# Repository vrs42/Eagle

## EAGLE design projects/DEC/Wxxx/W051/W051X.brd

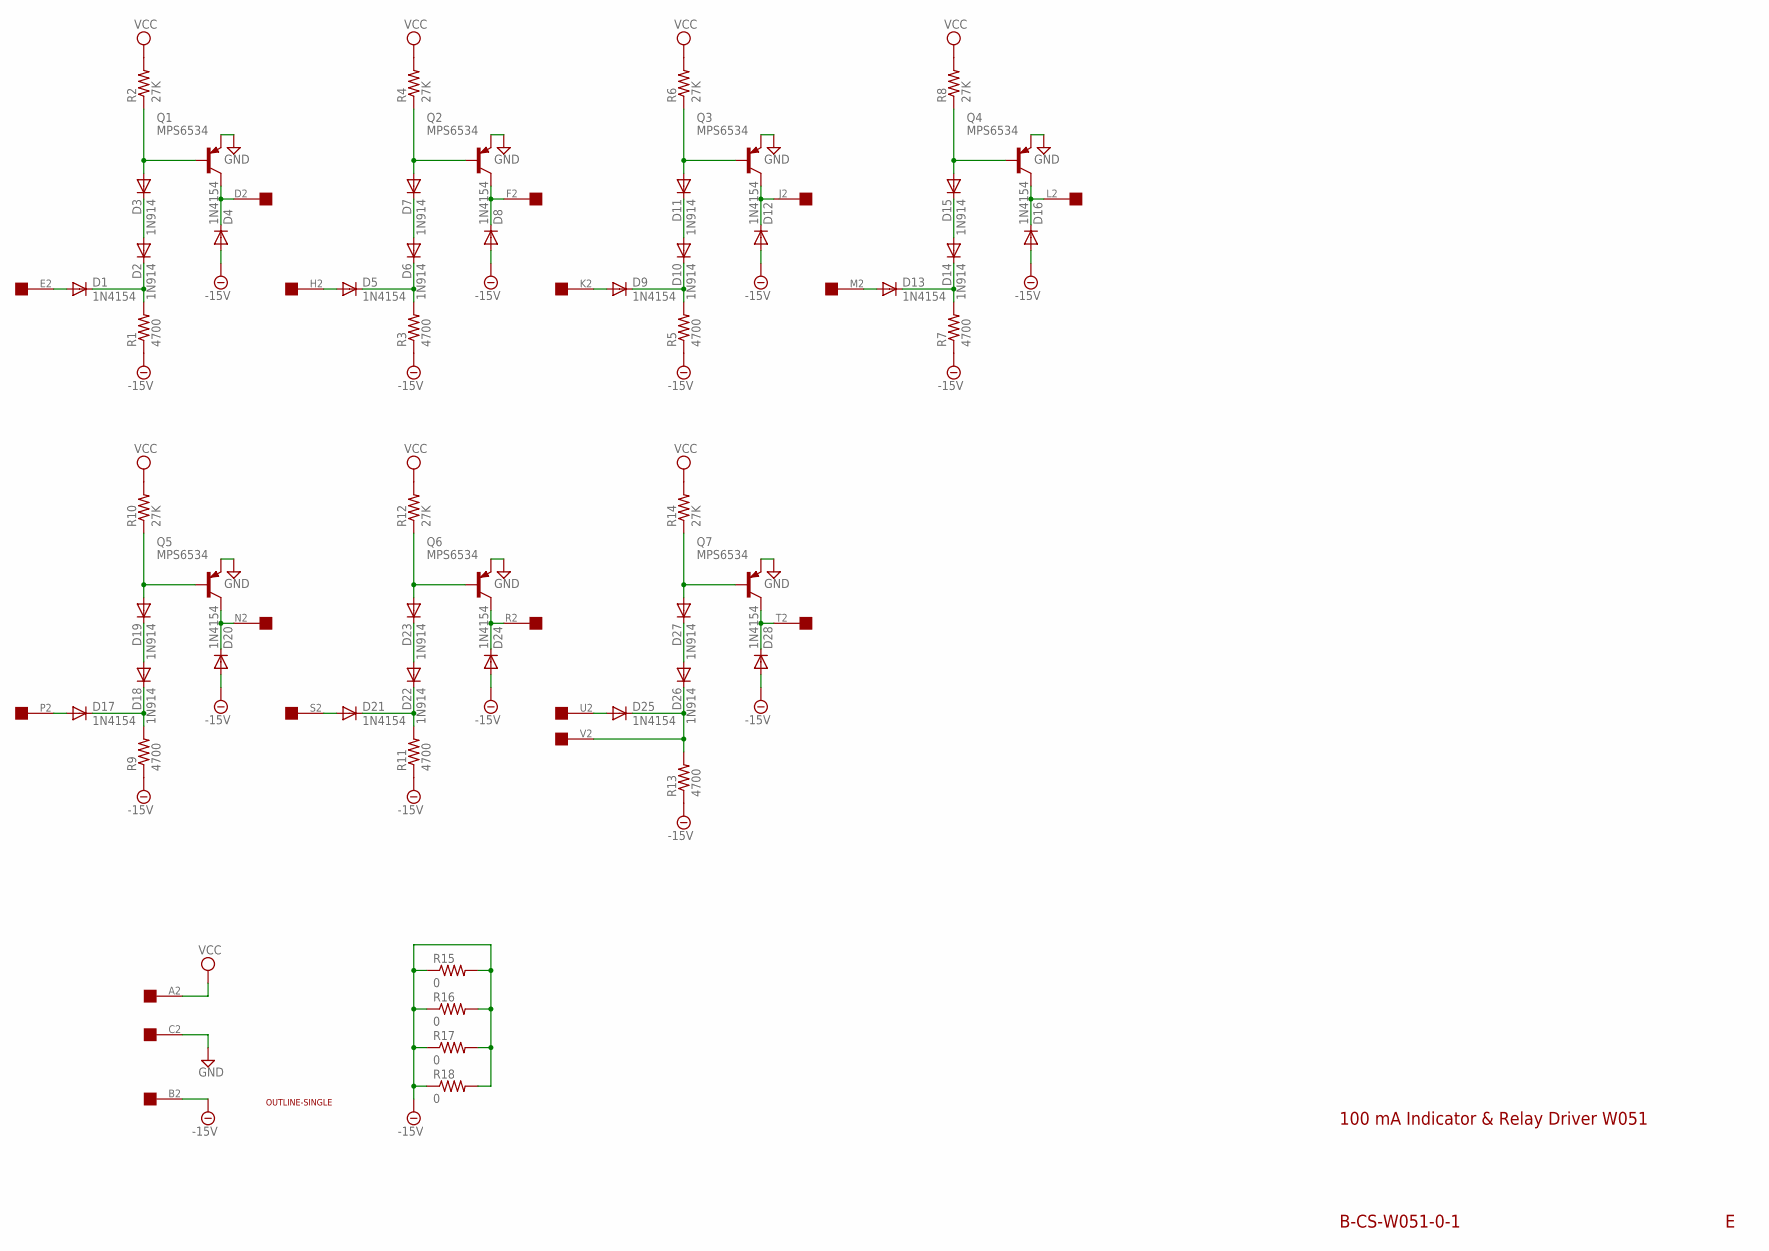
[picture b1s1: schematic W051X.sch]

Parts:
D1, D4, D5, D8, D9, D12, D13, D16, D17, D20, D21, D24, D25, D28: 1N4154; DO35-10
D2, D3, D6, D7, D10, D11, D14, D15, D18, D19, D22, D23, D26, D27: 1N914; DO35-10
Q1, Q2, Q3, Q4, Q5, Q6, Q7: MPS6534; TO5
R1, R3, R5, R7, R9, R11, R13: 4700; 0207/10
R2, R4, R6, R8, R10, R12, R14: 27K; 0207/10
R15, R16, R17, R18: 0; 0207/10
U$1: OUTLINE-SINGLE; SINGLE
U$2: EDGE-1; EDGE-CON1

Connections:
-15V: D4.A, D8.A, D12.A, D16.A, D20.A, D24.A, D28.A, R1.1, R3.1, R5.1, R7.1, R9.1, R11.1, R13.1, R15.1, R15.2, R16.1, R16.2, R17.1, R17.2, R18.1, R18.2, U$2.B2
GND: Q1.1 (E), Q2.1 (E), Q3.1 (E), Q4.1 (E), Q5.1 (E), Q6.1 (E), Q7.1 (E), U$2.C2
unnamed: D1.C, D2.C, R1.2
unnamed: D2.A, D3.C
unnamed: D3.A, Q1.2 (B), R2.1
unnamed: D4.C, Q1.3 (C), U$2.D2
unnamed: D1.A, U$2.E2
unnamed: D5.C, D6.C, R3.2
unnamed: D6.A, D7.C
unnamed: D7.A, Q2.2 (B), R4.1
unnamed: D8.C, Q2.3 (C), U$2.F2
unnamed: D5.A, U$2.H2
unnamed: D9.C, D10.C, R5.2
unnamed: D10.A, D11.C
unnamed: D11.A, Q3.2 (B), R6.1
unnamed: D12.C, Q3.3 (C), U$2.J2
unnamed: D9.A, U$2.K2
unnamed: D13.C, D14.C, R7.2
unnamed: D14.A, D15.C
unnamed: D15.A, Q4.2 (B), R8.1
unnamed: D16.C, Q4.3 (C), U$2.L2
unnamed: D13.A, U$2.M2
unnamed: D17.C, D18.C, R9.2
unnamed: D18.A, D19.C
unnamed: D19.A, Q5.2 (B), R10.1
unnamed: D28.C, Q7.3 (C), U$2.T2
unnamed: D17.A, U$2.P2
unnamed: D21.C, D22.C, R11.2
unnamed: D22.A, D23.C
unnamed: D23.A, Q6.2 (B), R12.1
unnamed: D24.C, Q6.3 (C), U$2.R2
unnamed: D21.A, U$2.S2
unnamed: D25.C, D26.C, R13.2, U$2.V2
unnamed: D26.A, D27.C
unnamed: D27.A, Q7.2 (B), R14.1
unnamed: D20.C, Q5.3 (C), U$2.N2
unnamed: D25.A, U$2.U2
VCC: R2.2, R4.2, R6.2, R8.2, R10.2, R12.2, R14.2, U$2.A2

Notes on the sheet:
B-CS-W051-0-1
100 mA Indicator & Relay Driver W051

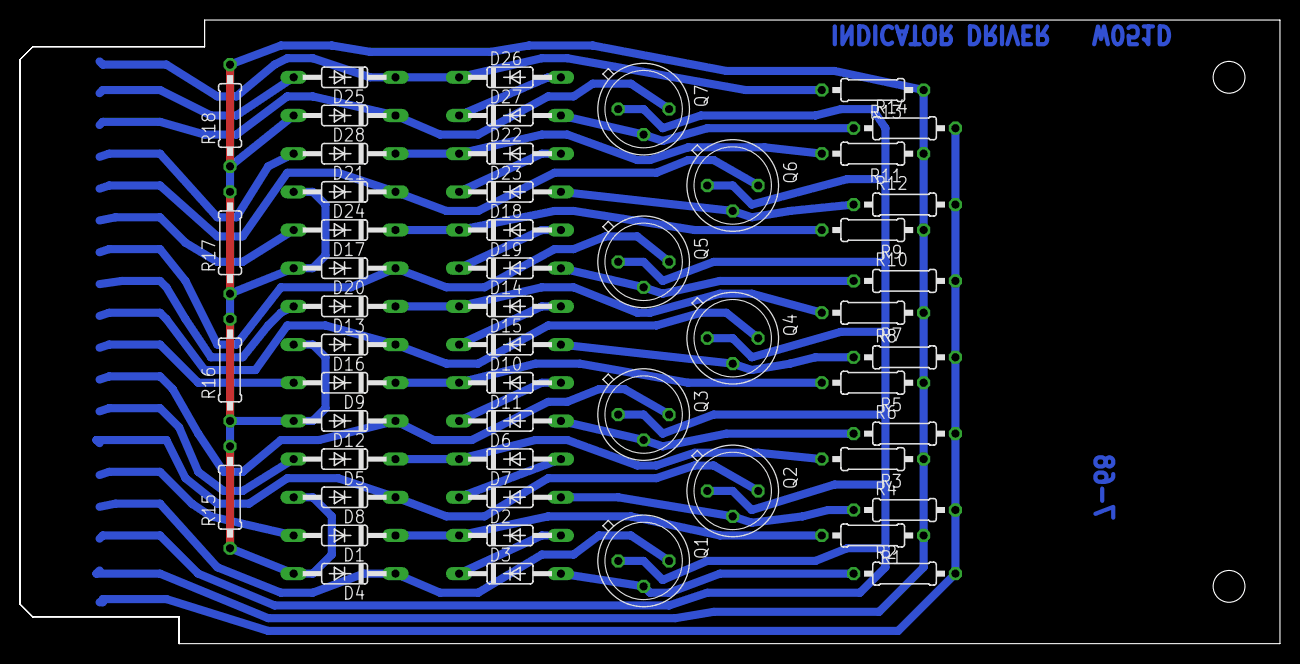
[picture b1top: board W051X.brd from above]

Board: 2 copper layers, 125.7 x 62.2 mm, 55 parts (0 on the bottom side), 38 nets.

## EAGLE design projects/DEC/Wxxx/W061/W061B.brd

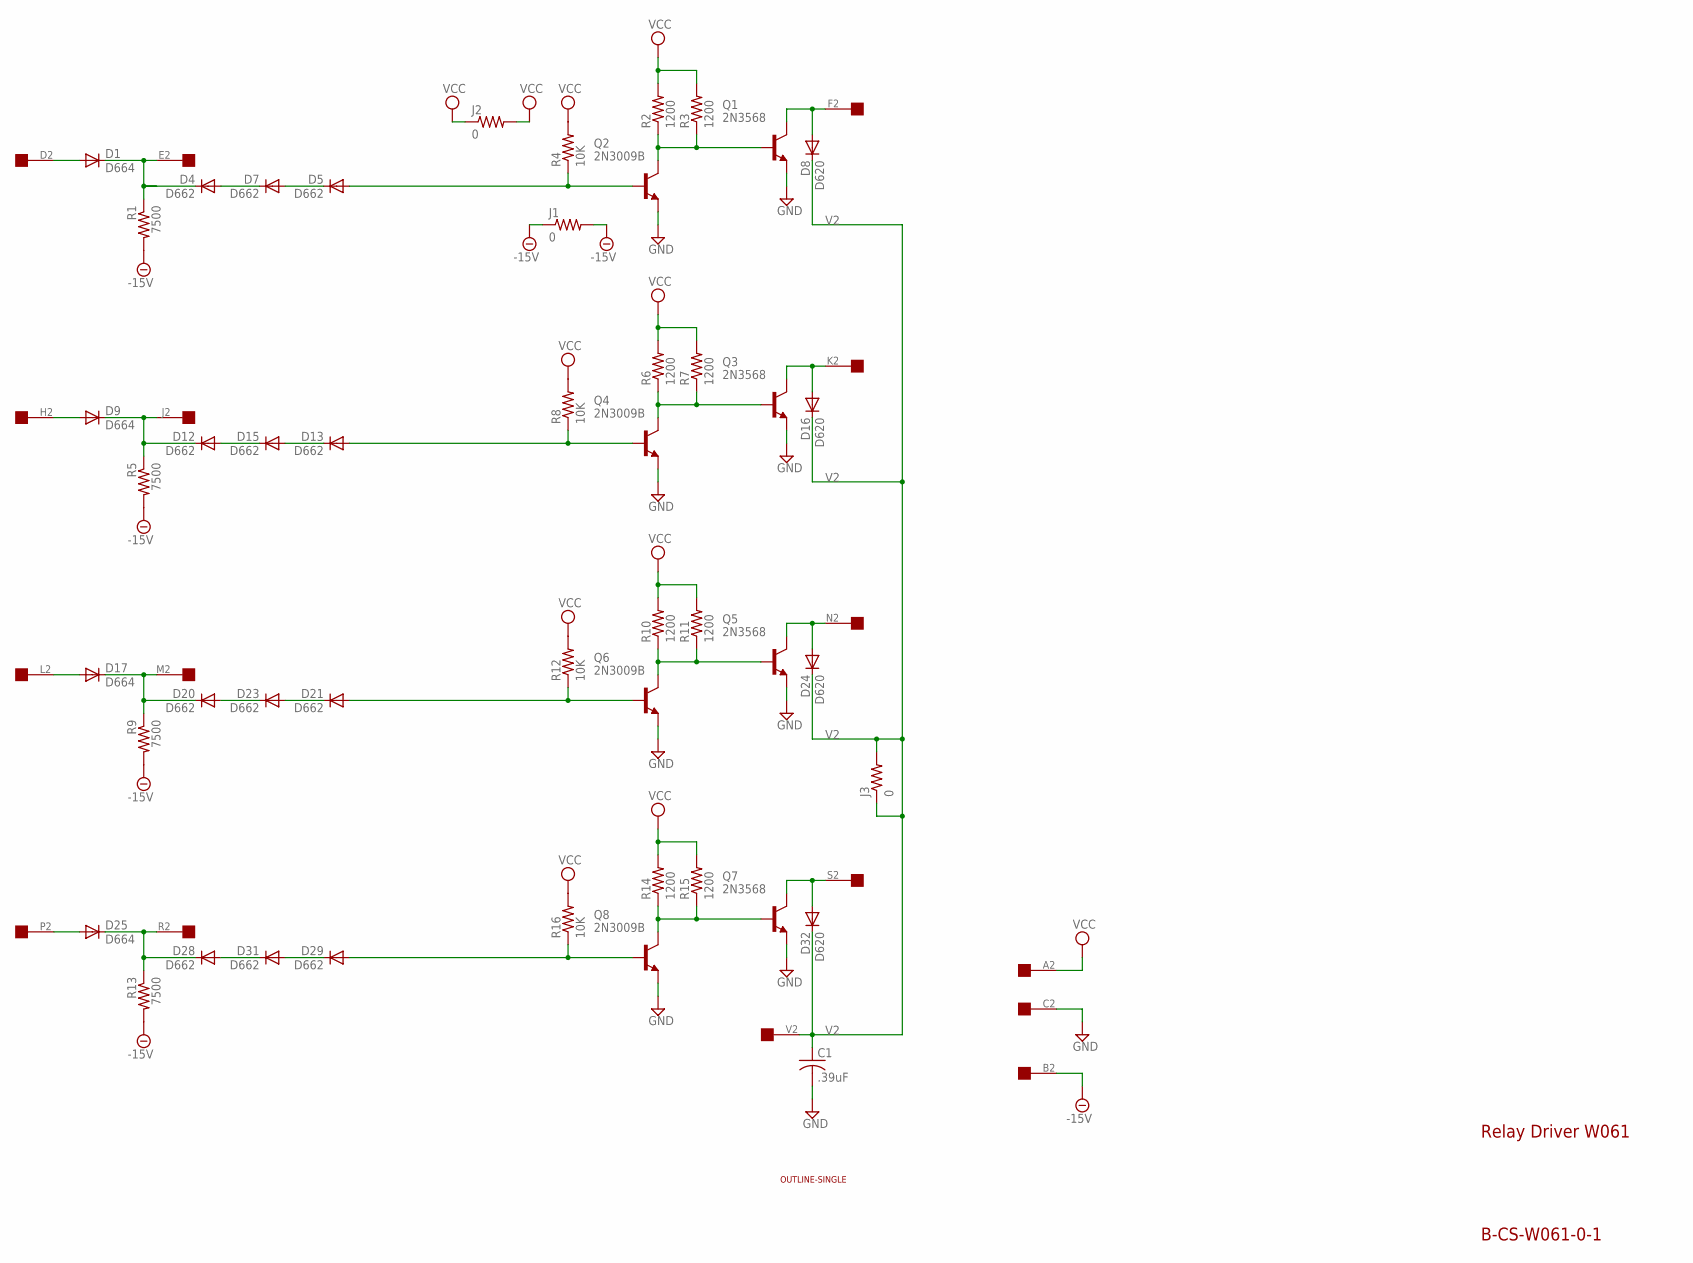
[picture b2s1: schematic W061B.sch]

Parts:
C1: .39uF; C375-155X418
D1, D9, D17, D25: D664; DO35-10
D4, D5, D7, D12, D13, D15, D20, D21, D23, D28, D29, D31: D662; DO35-10
D8, D16, D24, D32: D620; DO35-10
J1, J2, J3: 0; 0207/10
Q1, Q3, Q5, Q7: 2N3568; TO5
Q2, Q4, Q6, Q8: 2N3009B; TO5
R1, R5, R9, R13: 7500; 0207/10
R2, R3, R6, R7, R10, R11, R14, R15: 1200; 0207/10
R4, R8, R12, R16: 10K; 0207/10
U$1: OUTLINE-SINGLE; SINGLE
U$2: EDGE-1; EDGE-CON1

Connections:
-15V: J1.1, J1.2, R1.2, R5.2, R9.2, R13.2, U$2.B2
D2: D1.A, U$2.D2
E2: D1.C, D4.C, R1.1, U$2.E2
F2: D8.A, Q1.3 (C), U$2.F2
GND: C1.2, Q1.1 (E), Q2.1 (E), Q3.1 (E), Q4.1 (E), Q5.1 (E), Q6.1 (E), Q7.1 (E), Q8.1 (E), U$2.C2
H2: D9.A, U$2.H2
J2: D9.C, D12.C, R5.1, U$2.J2
K2: D16.A, Q3.3 (C), U$2.K2
L2: D17.A, U$2.L2
M2: D17.C, D20.C, R9.1, U$2.M2
N2: D24.A, Q5.3 (C), U$2.N2
unnamed: D13.A, Q4.2 (B), R8.1
unnamed: D5.A, Q2.2 (B), R4.1
unnamed: D5.C, D7.A
unnamed: D13.C, D15.A
unnamed: D4.A, D7.C
unnamed: D12.A, D15.C
unnamed: Q3.2 (B), Q4.3 (C), R6.1, R7.1
unnamed: Q1.2 (B), Q2.3 (C), R2.1, R3.1
unnamed: D21.A, Q6.2 (B), R12.1
unnamed: D21.C, D23.A
unnamed: D20.A, D23.C
unnamed: Q5.2 (B), Q6.3 (C), R10.1, R11.1
unnamed: D29.A, Q8.2 (B), R16.1
unnamed: D29.C, D31.A
unnamed: D28.A, D31.C
unnamed: Q7.2 (B), Q8.3 (C), R14.1, R15.1
P2: D25.A, U$2.P2
R2: D25.C, D28.C, R13.1, U$2.R2
S2: D32.A, Q7.3 (C), U$2.S2
V2: C1.1, D8.C, D16.C, D24.C, D32.C, J3.1, J3.2, U$2.V2
VCC: J2.1, J2.2, R2.2, R3.2, R4.2, R6.2, R7.2, R8.2, R10.2, R11.2, R12.2, R14.2, R15.2, R16.2, U$2.A2

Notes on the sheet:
Relay Driver W061
B-CS-W061-0-1

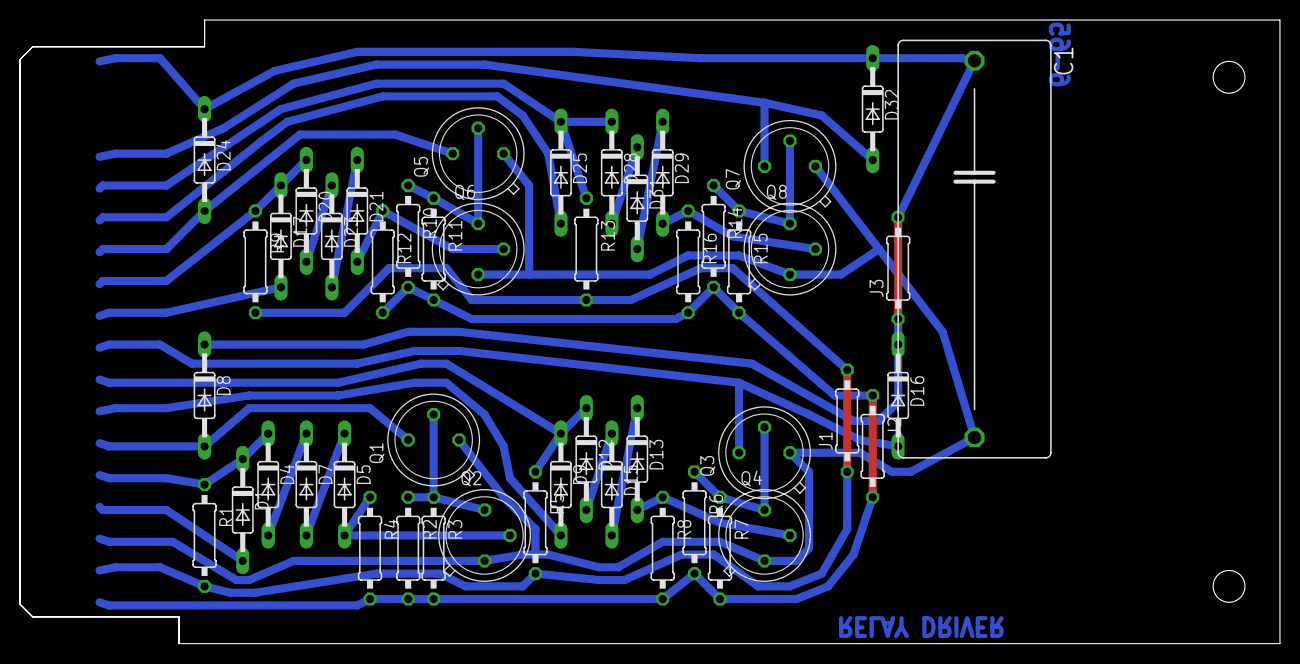
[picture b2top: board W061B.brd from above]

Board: 2 copper layers, 125.7 x 62.2 mm, 50 parts (0 on the bottom side), 32 nets.

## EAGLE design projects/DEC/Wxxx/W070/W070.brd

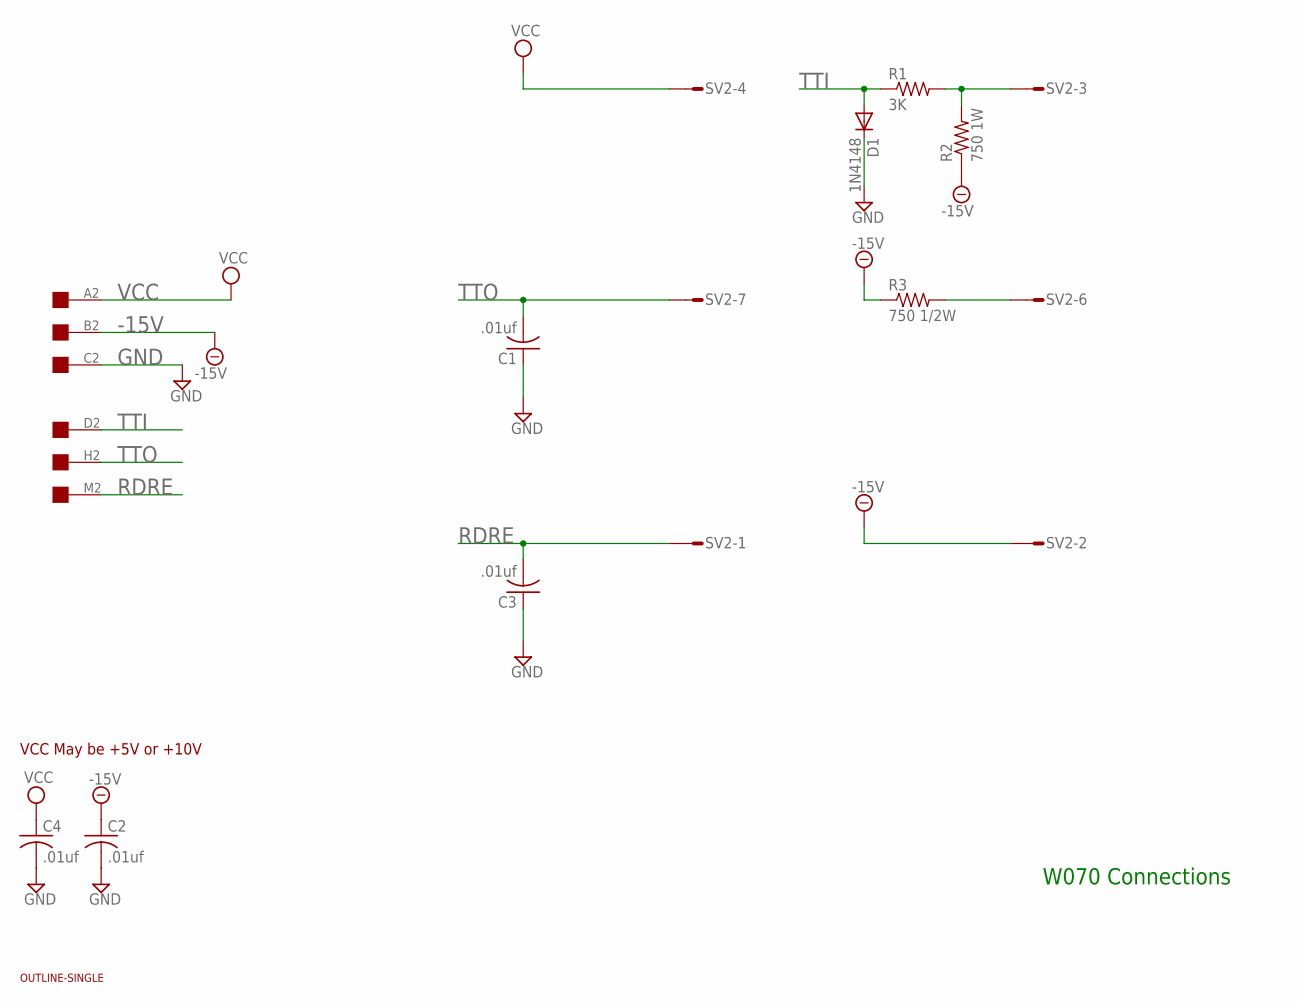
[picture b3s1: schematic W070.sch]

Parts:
C1, C2, C3, C4: .01uf; C050-025X075
D1: 1N4148; DO35-10
EDGE: EDGE-1; EDGE-CON1
R1: 3K; 0207/10
R2: 750 1W; 0309/12
R3: 750 1/2W; 0309/12
SV2: L08P
U$1: OUTLINE-SINGLE; SINGLE

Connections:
-15V: C2.1, EDGE.B2, R2.1, R3.1, SV2.2
GND: C1.1, C2.2, C3.1, C4.2, D1.C, EDGE.C2
unnamed: R3.2, SV2.6
unnamed: R1.2, R2.2, SV2.3
RDRE: C3.2, EDGE.M2, SV2.1
TTI: D1.A, EDGE.D2, R1.1
TTO: C1.2, EDGE.H2, SV2.7
VCC: C4.1, EDGE.A2, SV2.4

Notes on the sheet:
W070 Connections
VCC May be +5V or +10V

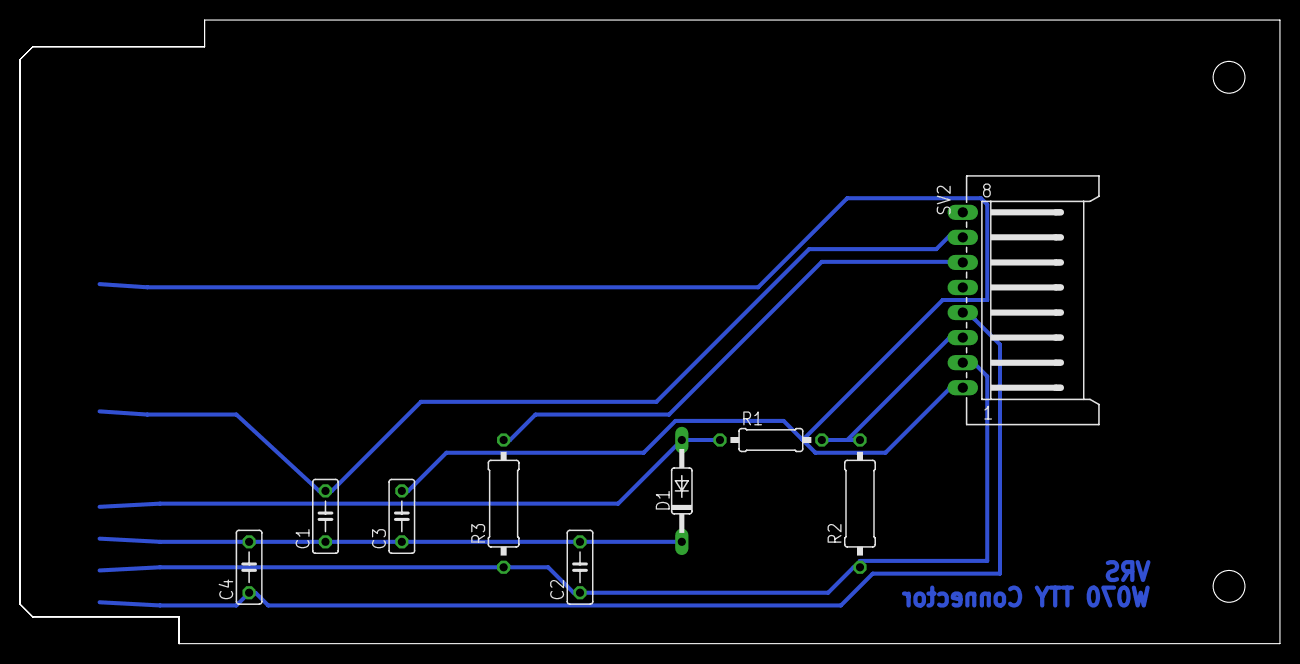
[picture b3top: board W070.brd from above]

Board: 2 copper layers, 125.7 x 62.2 mm, 11 parts (0 on the bottom side), 8 nets.

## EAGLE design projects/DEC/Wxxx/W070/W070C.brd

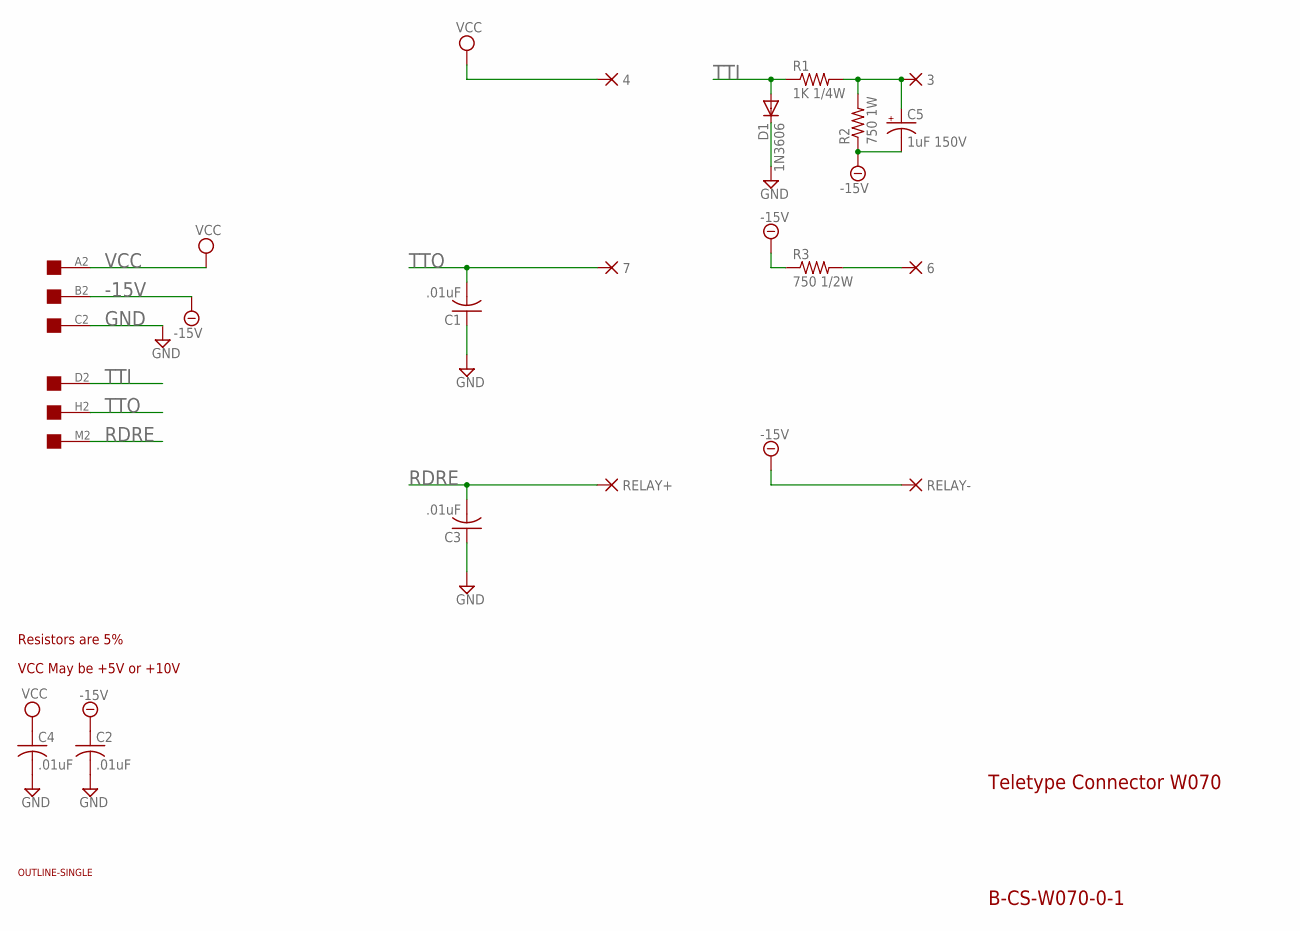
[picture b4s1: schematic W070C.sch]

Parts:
3, 4, 6, 7: PAD-0465; 0465
C1, C2, C3, C4: .01uF; C050-025X075
C5: 1uF 150V; E25-9
D1: 1N3606; DO35-10
EDGE: EDGE-1; EDGE-CON1
R1: 1K 1/4W; 0207/10
R2: 750 1W; 0411/12
R3: 750 1/2W; 0309/12
RELAY+: PAD-0465; 0465
RELAY-: PAD-0465; 0465
U$1: OUTLINE-SINGLE; SINGLE

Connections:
-15V: C2.1, C5.-, EDGE.B2, R2.1, R3.1, RELAY-.P$1
GND: C1.1, C2.2, C3.1, C4.2, D1.C, EDGE.C2
unnamed: 6.P$1, R3.2
unnamed: 3.P$1, C5.+, R1.2, R2.2
RDRE: C3.2, EDGE.M2, RELAY+.P$1
TTI: D1.A, EDGE.D2, R1.1
TTO: 7.P$1, C1.2, EDGE.H2
VCC: 4.P$1, C4.1, EDGE.A2

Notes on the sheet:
Teletype Connector W070
VCC May be +5V or +10V
Resistors are 5%
B-CS-W070-0-1

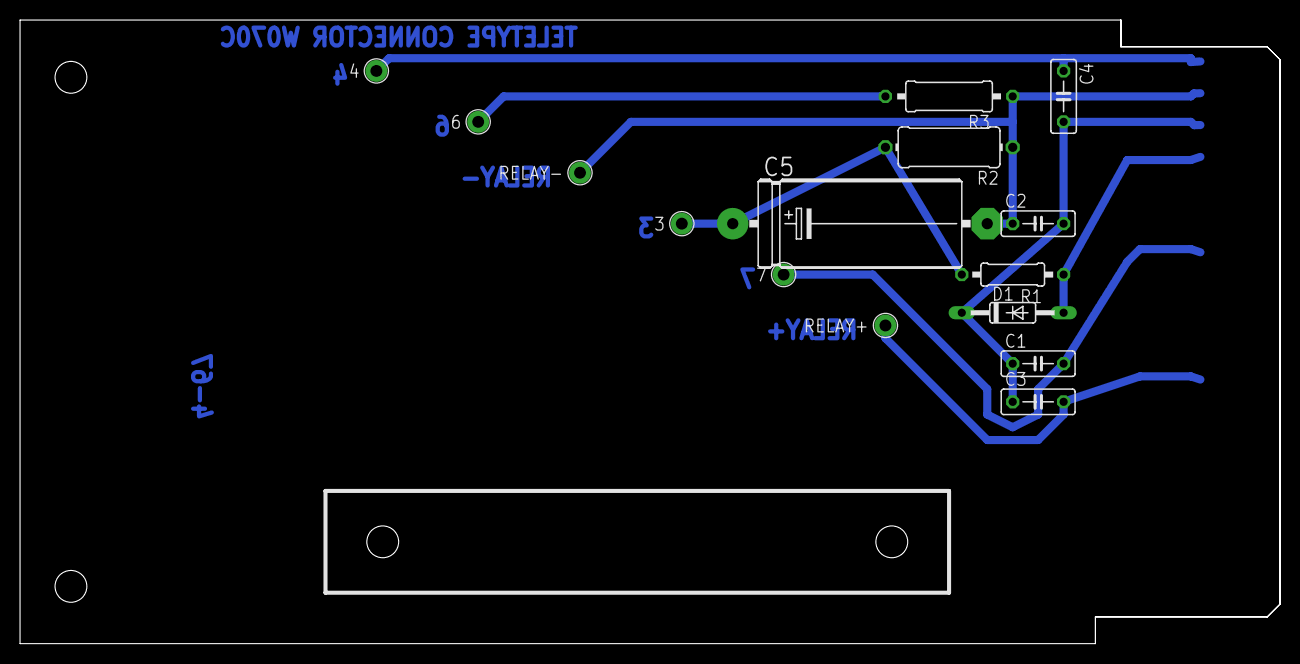
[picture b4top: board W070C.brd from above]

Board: 2 copper layers, 125.7 x 62.2 mm, 17 parts (0 on the bottom side), 8 nets.

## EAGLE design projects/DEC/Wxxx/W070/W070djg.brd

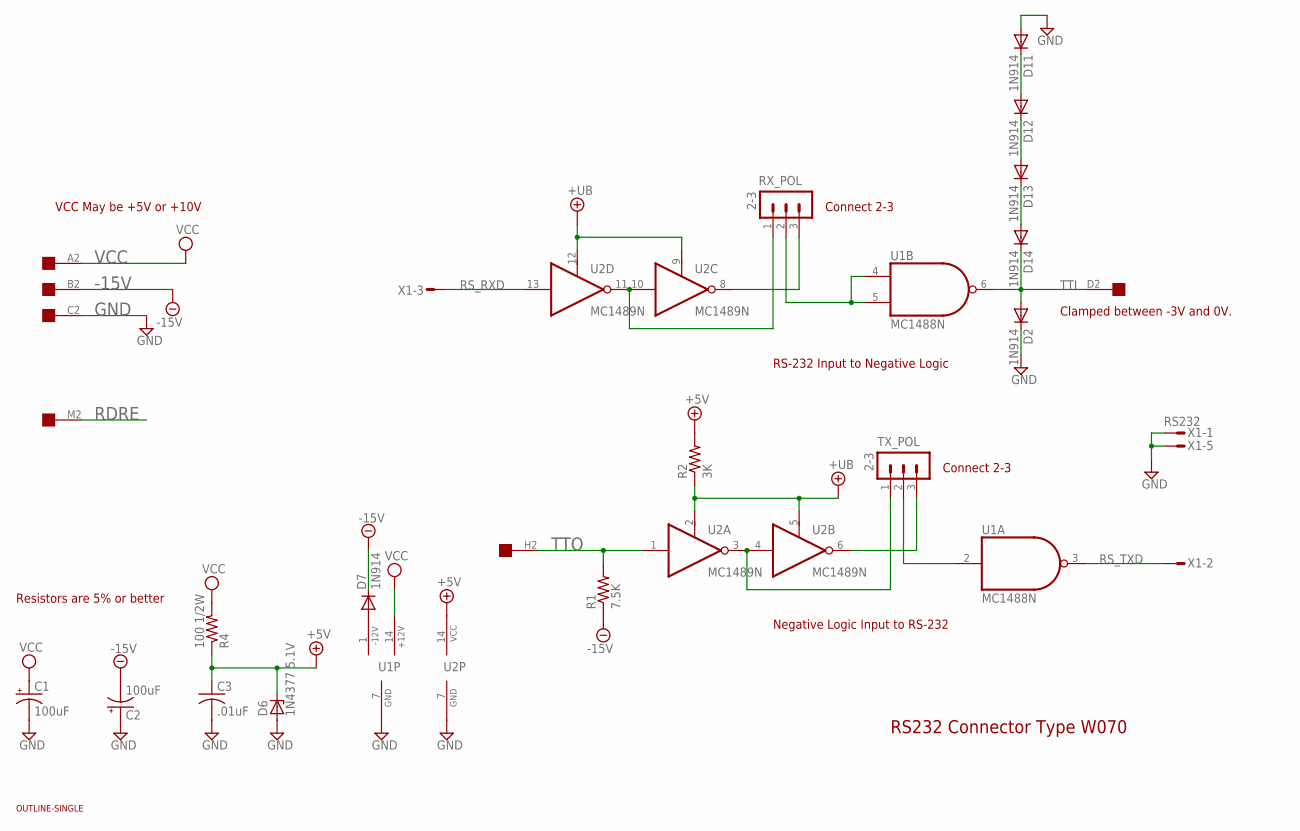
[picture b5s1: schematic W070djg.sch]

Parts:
C1, C2: 100uF; E22-9
C3: .01uF; C050-025X075
D2, D7, D11, D12, D13, D14: 1N914; DO35-10
D6: 1N4377 5.1V; DO35Z10
EDGE: EDGE-1; EDGE-CON1
R1: 7.5K; 0207/10
R2: 3K; 0207/10
R4: 100 1/2W; 0309/12
RX_POL: 2-3; MA03-1
TX_POL: 2-3; MA03-1
U1: MC1488N; DIL14
U2: MC1489N; DIL14
U$1: OUTLINE-SINGLE; SINGLE
X1: RS232; 182-009-MALE

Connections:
+5V: C3.1, D6.C, R2.2, R4.1, U2.14 (VCC)
+UB: R2.1, U2.2 (RC), U2.5 (RC), U2.9 (RC), U2.12 (RC)
-12V: D7.A, U1.1 (-12V)
-15V: C2.-, D7.C, EDGE.B2, R1.1
GND: C1.-, C2.+, C3.2, D2.C, D6.A, D11.A, EDGE.C2, U1.7 (GND), U2.7 (GND), X1.1, X1.5
unnamed: TX_POL.1, U2.3 (O), U2.4 (I)
unnamed: D13.C, D14.A
unnamed: D12.C, D13.A
unnamed: D11.C, D12.A
unnamed: TX_POL.3, U2.6 (O)
unnamed: TX_POL.2, U1.2 (I)
unnamed: RX_POL.1, U2.10 (I), U2.11 (O)
unnamed: RX_POL.2, U1.4 (I0), U1.5 (I1)
unnamed: RX_POL.3, U2.8 (O)
RDRE: EDGE.M2
RS_RXD: U2.13 (I), X1.3
RS_TXD: U1.3 (O), X1.2
TTI: D2.A, D14.C, EDGE.D2, U1.6 (O)
TTO: EDGE.H2, R1.2, U2.1 (I)
VCC: C1.+, EDGE.A2, R4.2, U1.14 (+12V)

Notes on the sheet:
RS232 Connector Type W070
VCC May be +5V or +10V
Resistors are 5% or better
RS-232 Input to Negative Logic
Clamped between -3V and 0V.
Negative Logic Input to RS-232
Connect 2-3

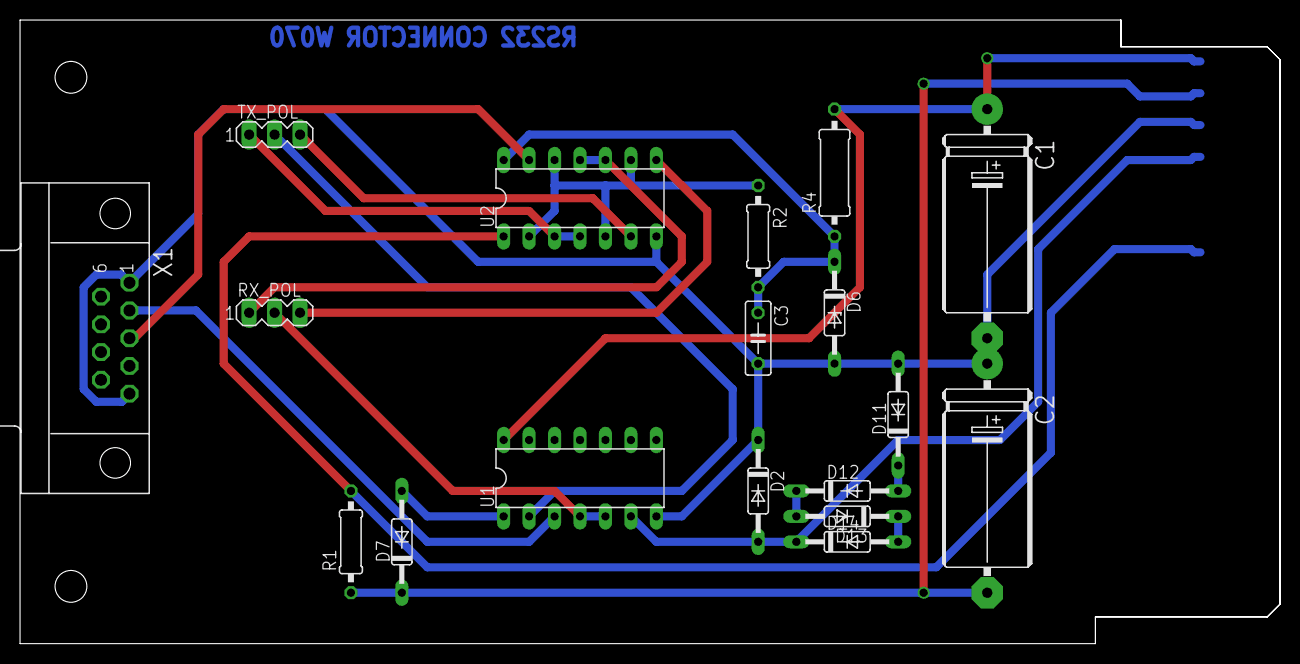
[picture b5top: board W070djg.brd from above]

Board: 2 copper layers, 125.7 x 62.2 mm, 20 parts (0 on the bottom side), 19 nets.
